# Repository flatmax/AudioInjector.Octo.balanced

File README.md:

# AudioInjector.Octo.balanced

The Audio Injector Octo sound card for the Raspberry Pi - differential powered breakouts. Find more information at : http://audioinjector.net

These KiCad (http://kicad.org/) files give both the schematic and PCB gerber layouts for the RCA breakouts for the Audio Injector Octo sound card.

These balanced breakout boards are based on Sallen-Key filters.

Matt Flax flatmax.com

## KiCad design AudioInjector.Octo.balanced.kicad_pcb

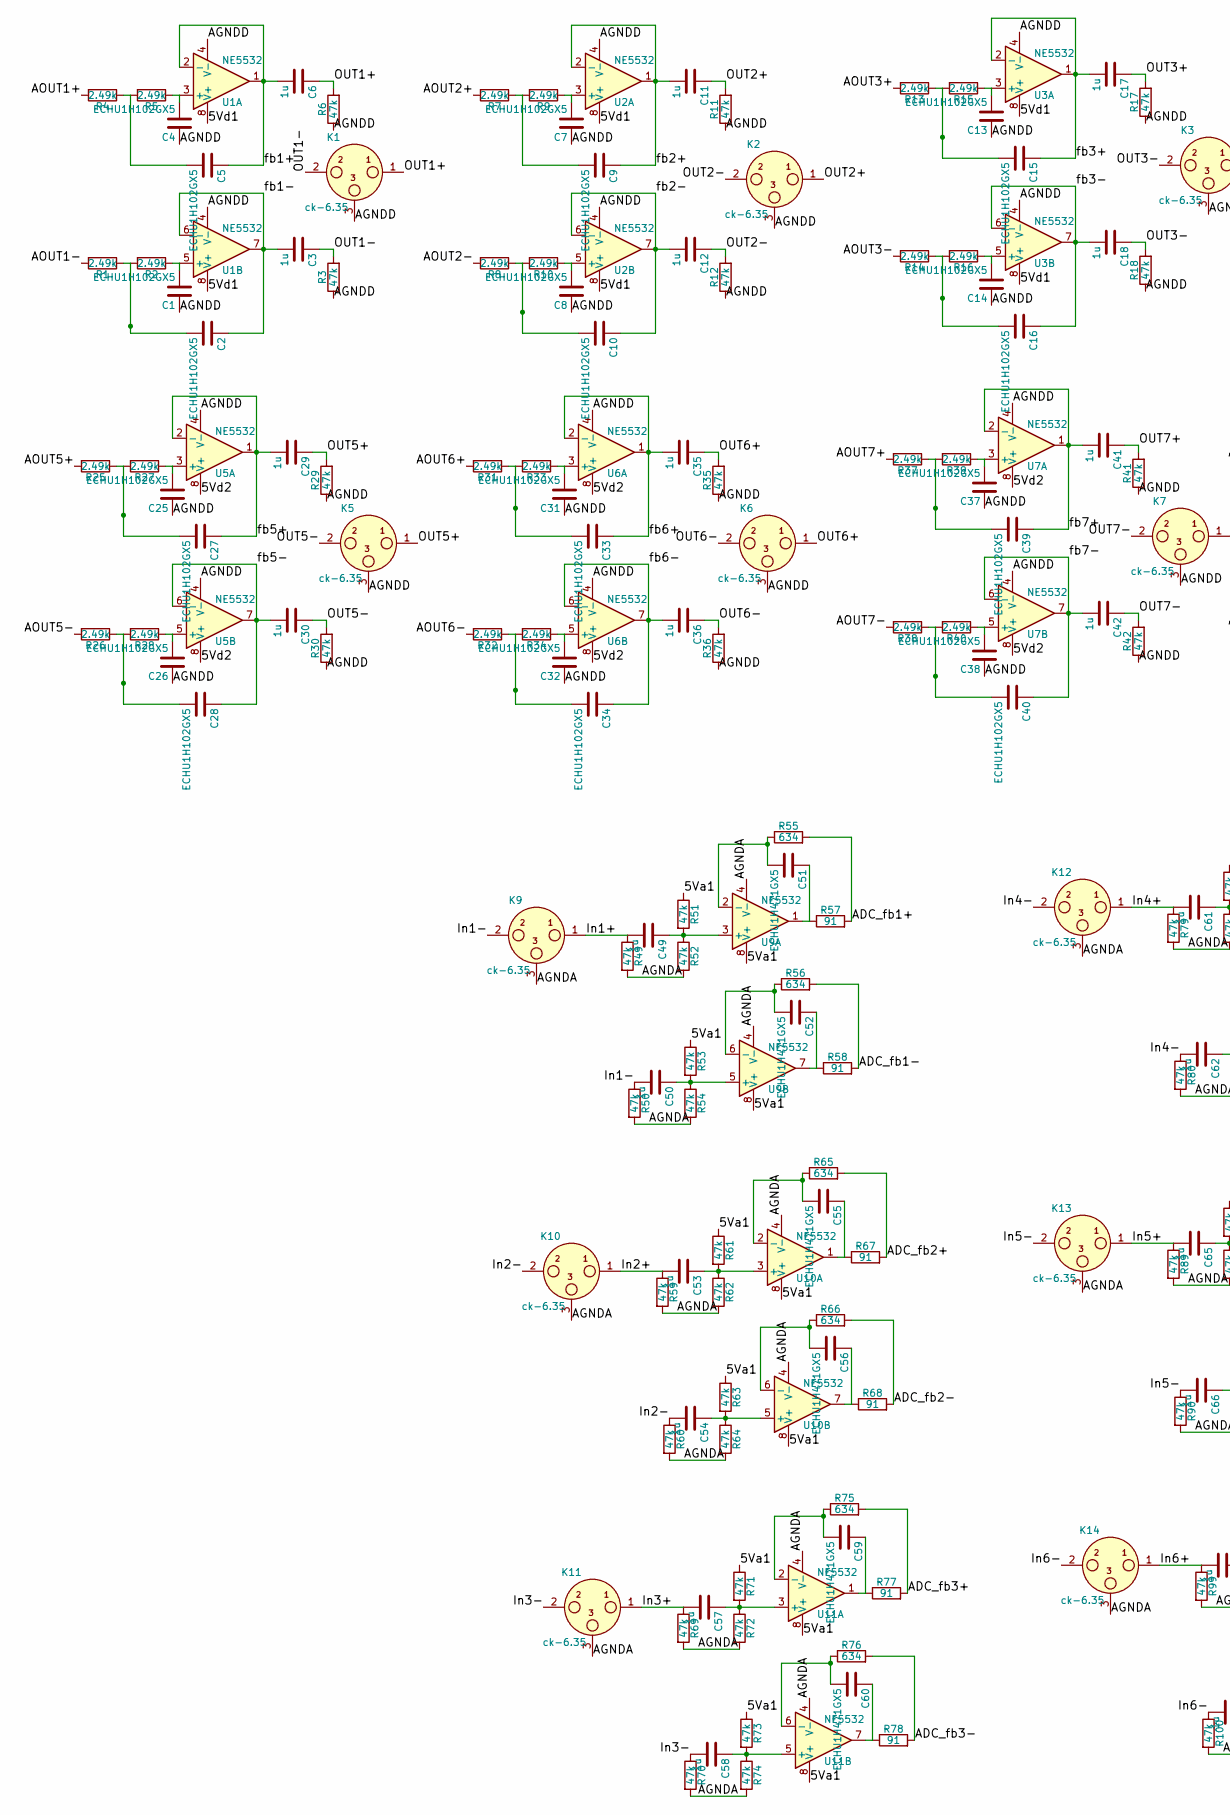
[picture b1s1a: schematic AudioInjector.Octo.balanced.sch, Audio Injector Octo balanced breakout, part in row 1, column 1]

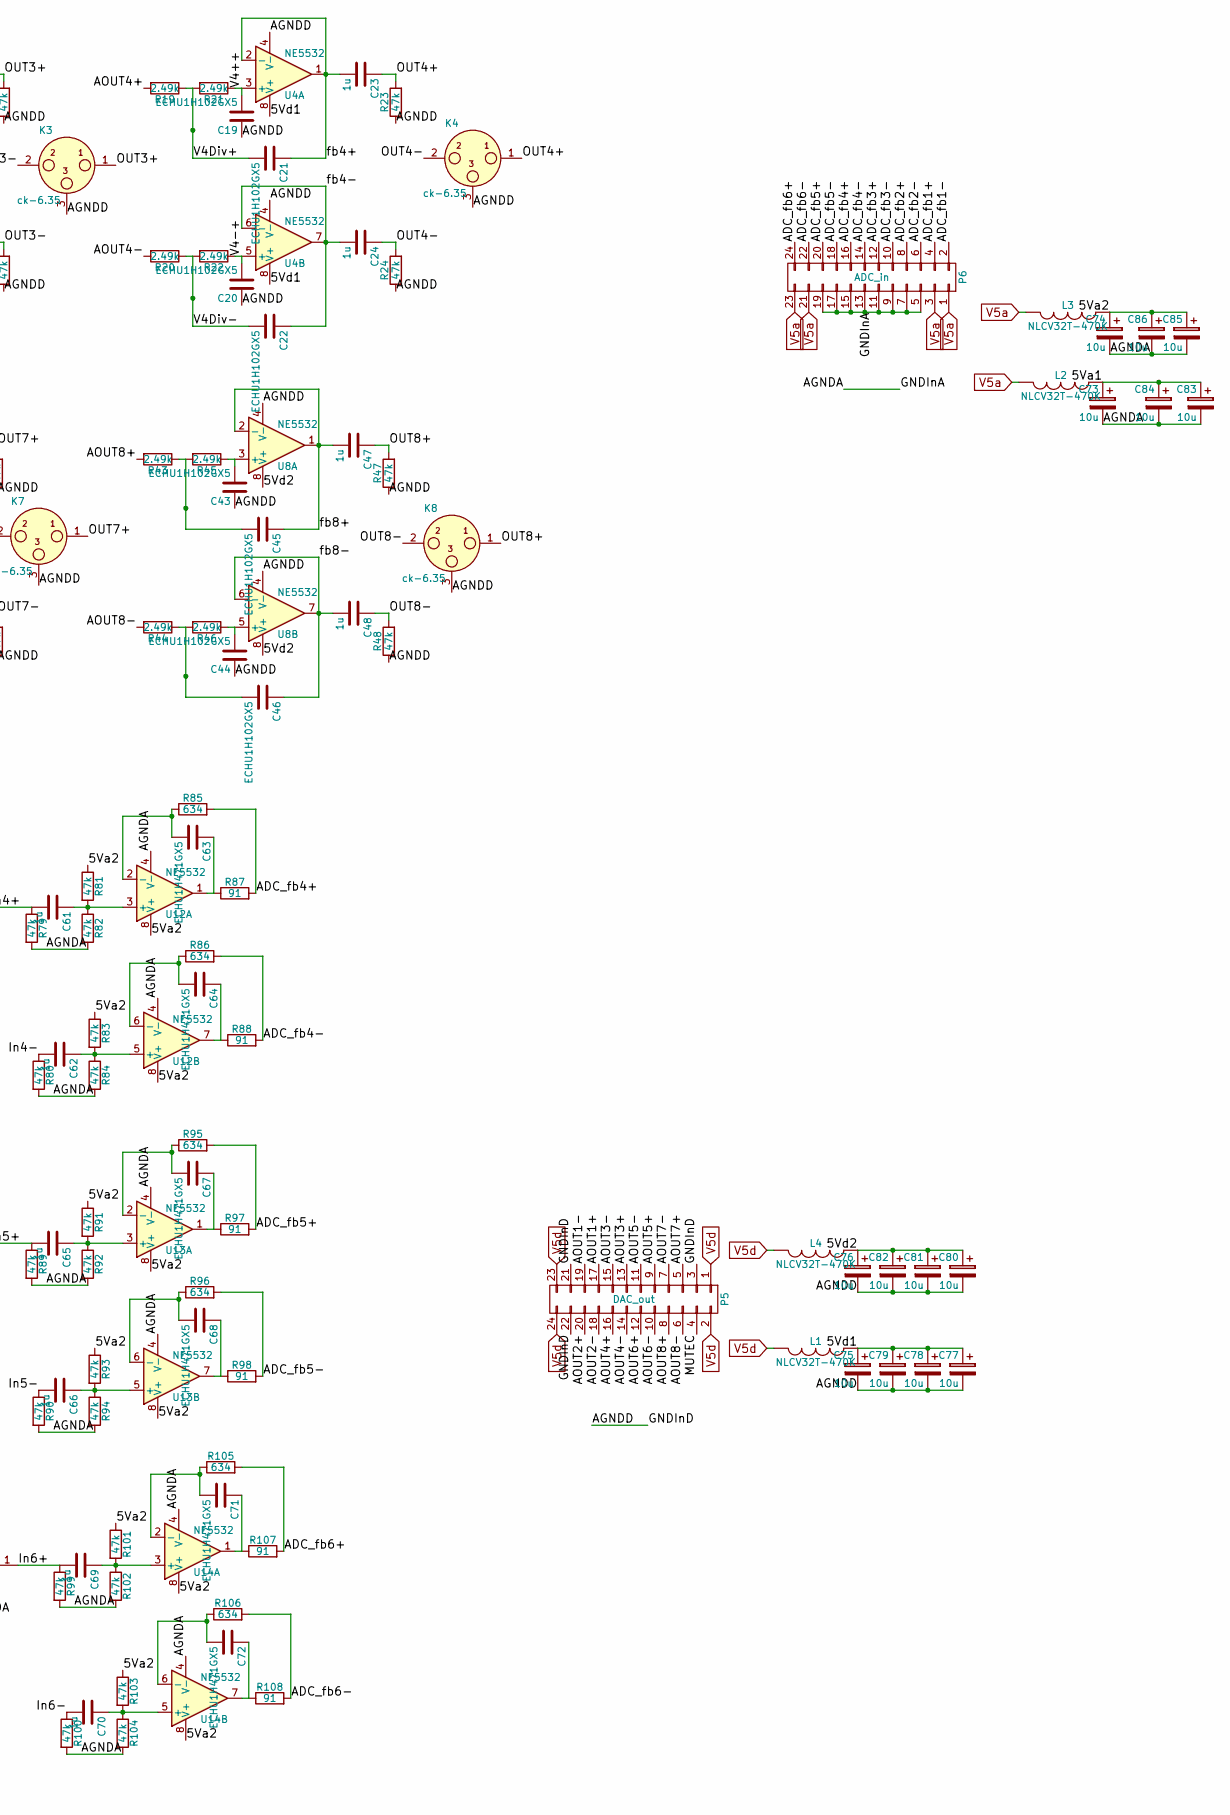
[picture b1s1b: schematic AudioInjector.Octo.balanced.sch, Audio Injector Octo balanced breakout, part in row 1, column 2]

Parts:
C1, C2, C4, C5, C7, C8, C9, C10, C13, C14, C15, C16, C19, C20, C21, C22, C25, C26, C27, C28, C31, C32, C33, C34, C37, C38, C39, C40, C43, C44, C45, C46: ECHU1H102GX5; C_0805
C3, C6, C11, C12, C17, C18, C23, C24, C29, C30, C35, C36, C41, C42, C47, C48, C49, C50, C53, C54, C57, C58, C61, C62, C65, C66, C69, C70: 1u; C_Rect_L7_W4.5_P5
C51, C52, C55, C56, C59, C60, C63, C64, C67, C68, C71, C72: ECHU1H471GX5; C_0805
C73, C74, C75, C76, C77, C78, C79, C80, C81, C82, C83, C84, C85, C86: 10u; c_elec_4x5.3
K1, K2, K3, K4, K5, K6, K7, K8: ck-6.35; 334g_6p_noThru
K9, K10, K11, K12, K13, K14: ck-6.35; 334g_6p
L1, L2, L3, L4: NLCV32T-470K; Neosid_Inductor_SM-NE30_SMD1210
P5: DAC_out; Pin_Header_Straight_2x12
P6: ADC_in; Pin_Header_Straight_2x12
R1, R2, R4, R5, R7, R8, R9, R10, R13, R14, R15, R16, R19, R20, R21, R22, R25, R26, R27, R28, R31, R32, R33, R34, R37, R38, R39, R40, R43, R44, R45, R46: 2.49k; R_0603
R3, R6, R11, R12, R17, R18, R23, R24, R29, R30, R35, R36, R41, R42, R47, R48, R49, R50, R51, R52, R53, R54, R59, R60, R61, R62, R63, R64, R69, R70, R71, R72, R73, R74, R79, R80, R81, R82, R83, R84, R89, R90, R91, R92, R93, R94, R99, R100, R101, R102, R103, R104: 47k; R_0603
R55, R56, R65, R66, R75, R76, R85, R86, R95, R96, R105, R106: 634; R_0603
R57, R58, R67, R68, R77, R78, R87, R88, R97, R98, R107, R108: 91; R_0603
U1, U2, U3, U4, U5, U6, U7, U8, U9, U10, U11, U12, U13, U14: NE5532; SOIC-8-N

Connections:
/5Va1: C73.1, C83.1, C84.1, L2.2, R51.1, R53.1, R61.1, R63.1, R71.1, R73.1, U9.8 (V+), U10.8 (V+), U11.8 (V+)
/5Va2: C74.1, C85.1, C86.1, L3.2, R81.1, R83.1, R91.1, R93.1, R101.1, R103.1, U12.8 (V+), U13.8 (V+), U14.8 (V+)
/5Vd1: C75.1, C77.1, C78.1, C79.1, L1.2, U1.8 (V+), U2.8 (V+), U3.8 (V+), U4.8 (V+)
/5Vd2: C76.1, C80.1, C81.1, C82.1, L4.2, U5.8 (V+), U6.8 (V+), U7.8 (V+), U8.8 (V+)
/ADC_fb1+: P6.4, R55.2, R57.2
/ADC_fb1-: P6.2, R56.2, R58.2
/ADC_fb2+: P6.8, R65.2, R67.2
/ADC_fb2-: P6.6, R66.2, R68.2
/ADC_fb3+: P6.12, R75.2, R77.2
/ADC_fb3-: P6.10, R76.2, R78.2
/ADC_fb4+: P6.16, R85.2, R87.2
/ADC_fb4-: P6.14, R86.2, R88.2
/ADC_fb5+: P6.20, R95.2, R97.2
/ADC_fb5-: P6.18, R96.2, R98.2
/ADC_fb6+: P6.24, R105.2, R107.2
/ADC_fb6-: P6.22, R106.2, R108.2
/AGNDA: C73.2, C74.2, C83.2, C84.2, C85.2, C86.2, K9.3, K10.3, K11.3, K12.3, K13.3, K14.3, P6.5, P6.7, P6.9, P6.11, P6.13, P6.15, P6.17, P6.19, R49.2, R50.2, R52.2, R54.2, R59.2, R60.2, R62.2, R64.2, R69.2, R70.2, R72.2, R74.2, R79.2, R80.2, R82.2, R84.2, R89.2, R90.2, R92.2, R94.2, R99.2, R100.2, R102.2, R104.2, U9.4 (V-), U10.4 (V-), U11.4 (V-), U12.4 (V-), U13.4 (V-), U14.4 (V-)
/AGNDD: C1.1, C4.1, C7.1, C8.1, C13.1, C14.1, C19.1, C20.1, C25.1, C26.1, C31.1, C32.1, C37.1, C38.1, C43.1, C44.1, C75.2, C76.2, C77.2, C78.2, C79.2, C80.2, C81.2, C82.2, K1.3, K2.3, K3.3, K4.3, K5.3, K6.3, K7.3, K8.3, P5.3, P5.21, P5.22, R3.1, R6.1, R11.1, R12.1, R17.1, R18.1, R23.1, R24.1, R29.1, R30.1, R35.1, R36.1, R41.1, R42.1, R47.1, R48.1, U1.4 (V-), U2.4 (V-), U3.4 (V-), U4.4 (V-), U5.4 (V-), U6.4 (V-), U7.4 (V-), U8.4 (V-)
/AOUT1+: P5.17, R4.2
/AOUT1-: P5.19, R1.2
/AOUT2+: P5.20, R7.2
/AOUT2-: P5.18, R8.2
/AOUT3+: P5.13, R13.2
/AOUT3-: P5.15, R14.2
/AOUT4+: P5.16, R19.2
/AOUT4-: P5.14, R20.2
/AOUT5+: P5.9, R25.2
/AOUT5-: P5.11, R26.2
/AOUT6+: P5.12, R31.2
/AOUT6-: P5.10, R32.2
/AOUT7+: P5.5, R37.2
/AOUT7-: P5.7, R38.2
/AOUT8+: P5.8, R43.2
/AOUT8-: P5.6, R44.2
/In1+: C49.2, K9.1, R49.1
/In1-: C50.2, K9.2, R50.1
/In2+: C53.2, K10.1, R59.1
/In2-: C54.2, K10.2, R60.1
/In3+: C57.2, K11.1, R69.1
/In3-: C58.2, K11.2, R70.1
/In4+: C61.2, K12.1, R79.1
/In4-: C62.2, K12.2, R80.1
/In5+: C65.2, K13.1, R89.1
/In5-: C66.2, K13.2, R90.1
/In6+: C69.2, K14.1, R99.1
/In6-: C70.2, K14.2, R100.1
/OUT1+: C6.1, K1.1, R6.2
/OUT1-: C3.1, K1.2, R3.2
/OUT2+: C11.1, K2.1, R11.2
/OUT2-: C12.1, K2.2, R12.2
/OUT3+: C17.1, K3.1, R17.2
/OUT3-: C18.1, K3.2, R18.2
/OUT4+: C23.1, K4.1, R23.2
/OUT4-: C24.1, K4.2, R24.2
/OUT5+: C29.1, K5.1, R29.2
/OUT5-: C30.1, K5.2, R30.2
/OUT6+: C35.1, K6.1, R35.2
/OUT6-: C36.1, K6.2, R36.2
/OUT7+: C41.1, K7.1, R41.2
/OUT7-: C42.1, K7.2, R42.2
/OUT8+: C47.1, K8.1, R47.2
/OUT8-: C48.1, K8.2, R48.2
/V4++: C19.2, R21.1, U4.3 (+)
/V4-+: C20.2, R22.1, U4.5 (+)
/V4Div+: C21.2, R19.1, R21.2
/V4Div-: C22.2, R20.1, R22.2
/fb1+: C5.1, C6.2, U1.1, U1.2 (-)
/fb1-: C2.1, C3.2, U1.6 (-), U1.7
/fb2+: C9.1, C11.2, U2.1, U2.2 (-)
/fb2-: C10.1, C12.2, U2.6 (-), U2.7
/fb3+: C15.1, C17.2, U3.1, U3.2 (-)
/fb3-: C16.1, C18.2, U3.6 (-), U3.7
/fb4+: C21.1, C23.2, U4.1, U4.2 (-)
/fb4-: C22.1, C24.2, U4.6 (-), U4.7
/fb5+: C27.1, C29.2, U5.1, U5.2 (-)
/fb5-: C28.1, C30.2, U5.6 (-), U5.7
/fb6+: C33.1, C35.2, U6.1, U6.2 (-)
/fb6-: C34.1, C36.2, U6.6 (-), U6.7
/fb7+: C39.1, C41.2, U7.1, U7.2 (-)
/fb7-: C40.1, C42.2, U7.6 (-), U7.7
/fb8+: C45.1, C47.2, U8.1, U8.2 (-)
/fb8-: C46.1, C48.2, U8.6 (-), U8.7
unnamed: C1.2, R2.1, U1.5 (+)
unnamed: C2.2, R1.1, R2.2
unnamed: C4.2, R5.1, U1.3 (+)
unnamed: C5.2, R4.1, R5.2
unnamed: C7.2, R9.1, U2.3 (+)
unnamed: C8.2, R10.1, U2.5 (+)
unnamed: C9.2, R7.1, R9.2
unnamed: C10.2, R8.1, R10.2
unnamed: C13.2, R15.1, U3.3 (+)
unnamed: C14.2, R16.1, U3.5 (+)
unnamed: C15.2, R13.1, R15.2
unnamed: C16.2, R14.1, R16.2
unnamed: C25.2, R27.1, U5.3 (+)
unnamed: C26.2, R28.1, U5.5 (+)
unnamed: C27.2, R25.1, R27.2
unnamed: C28.2, R26.1, R28.2
unnamed: C31.2, R33.1, U6.3 (+)
unnamed: C32.2, R34.1, U6.5 (+)
unnamed: C33.2, R31.1, R33.2
unnamed: C34.2, R32.1, R34.2
unnamed: C37.2, R39.1, U7.3 (+)
unnamed: C38.2, R40.1, U7.5 (+)
unnamed: C39.2, R37.1, R39.2
unnamed: C40.2, R38.1, R40.2
unnamed: C43.2, R45.1, U8.3 (+)
unnamed: C44.2, R46.1, U8.5 (+)
unnamed: C45.2, R43.1, R45.2
unnamed: C46.2, R44.1, R46.2
unnamed: C49.1, R51.2, R52.1, U9.3 (+)
unnamed: C50.1, R53.2, R54.1, U9.5 (+)
unnamed: C51.1, R57.1, U9.1
unnamed: C51.2, R55.1, U9.2 (-)
unnamed: C52.1, R58.1, U9.7
unnamed: C52.2, R56.1, U9.6 (-)
unnamed: C53.1, R61.2, R62.1, U10.3 (+)
unnamed: C54.1, R63.2, R64.1, U10.5 (+)
unnamed: C55.1, R67.1, U10.1
unnamed: C55.2, R65.1, U10.2 (-)
unnamed: C56.1, R68.1, U10.7
unnamed: C56.2, R66.1, U10.6 (-)
unnamed: C57.1, R71.2, R72.1, U11.3 (+)
unnamed: C58.1, R73.2, R74.1, U11.5 (+)
unnamed: C59.1, R77.1, U11.1
unnamed: C59.2, R75.1, U11.2 (-)
unnamed: C60.1, R78.1, U11.7
unnamed: C60.2, R76.1, U11.6 (-)
unnamed: C61.1, R81.2, R82.1, U12.3 (+)
unnamed: C62.1, R83.2, R84.1, U12.5 (+)
unnamed: C63.1, R87.1, U12.1
unnamed: C63.2, R85.1, U12.2 (-)
unnamed: C64.1, R88.1, U12.7
unnamed: C64.2, R86.1, U12.6 (-)
unnamed: C65.1, R91.2, R92.1, U13.3 (+)
unnamed: C66.1, R93.2, R94.1, U13.5 (+)
unnamed: C67.1, R97.1, U13.1
unnamed: C67.2, R95.1, U13.2 (-)
unnamed: C68.1, R98.1, U13.7
unnamed: C68.2, R96.1, U13.6 (-)
unnamed: C69.1, R101.2, R102.1, U14.3 (+)
unnamed: C70.1, R103.2, R104.1, U14.5 (+)
unnamed: C71.1, R107.1, U14.1
unnamed: C71.2, R105.1, U14.2 (-)
unnamed: C72.1, R108.1, U14.7
unnamed: C72.2, R106.1, U14.6 (-)
V5a: L2.1, L3.1, P6.1, P6.3, P6.21, P6.23
V5d: L1.1, L4.1, P5.1, P5.2, P5.23, P5.24

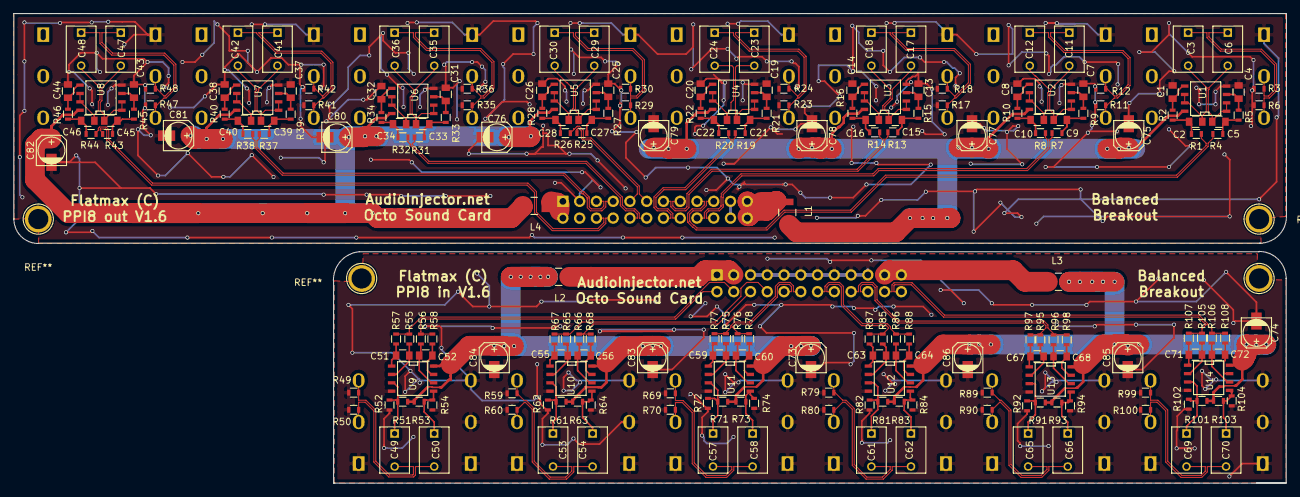
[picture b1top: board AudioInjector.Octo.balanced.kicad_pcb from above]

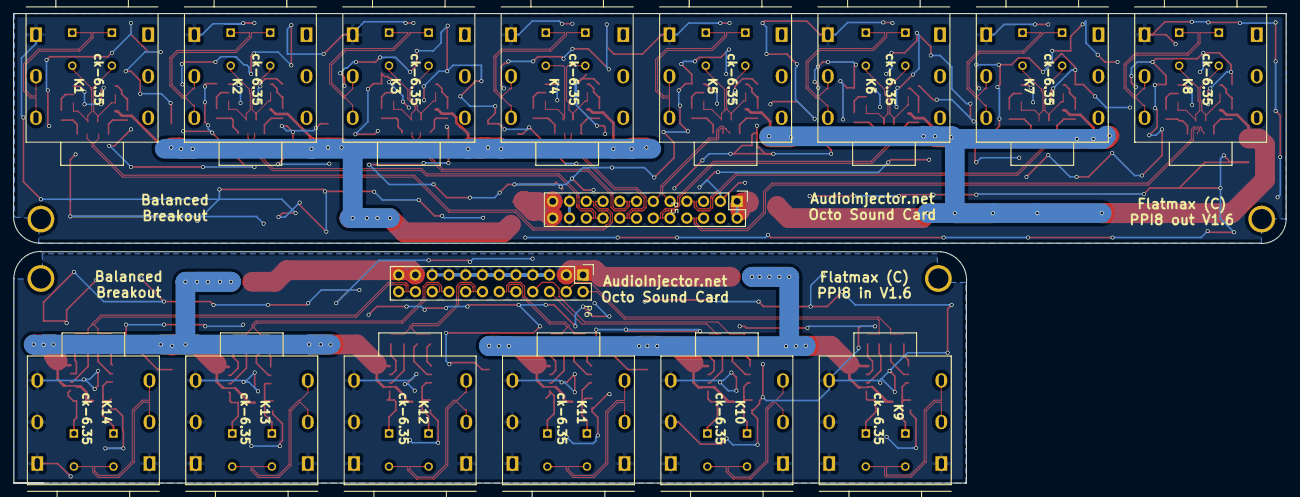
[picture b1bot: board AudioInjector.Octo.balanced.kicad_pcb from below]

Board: 2 copper layers, 192.9 x 71.2 mm, 228 parts (16 on the bottom side), 148 nets.

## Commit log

2017-02-17 V1.3
2017-06-22 V1.6 of the balanced breakout for the Audioinjector Octo sound card for the Pi.
2017-09-28 Added the schematic pdf.
2021-11-09 Update README.md
    https://forum.kicad.info/t/warning-avoid-all-links-to-kicad-pcb-org-use-kicad-org/31521
